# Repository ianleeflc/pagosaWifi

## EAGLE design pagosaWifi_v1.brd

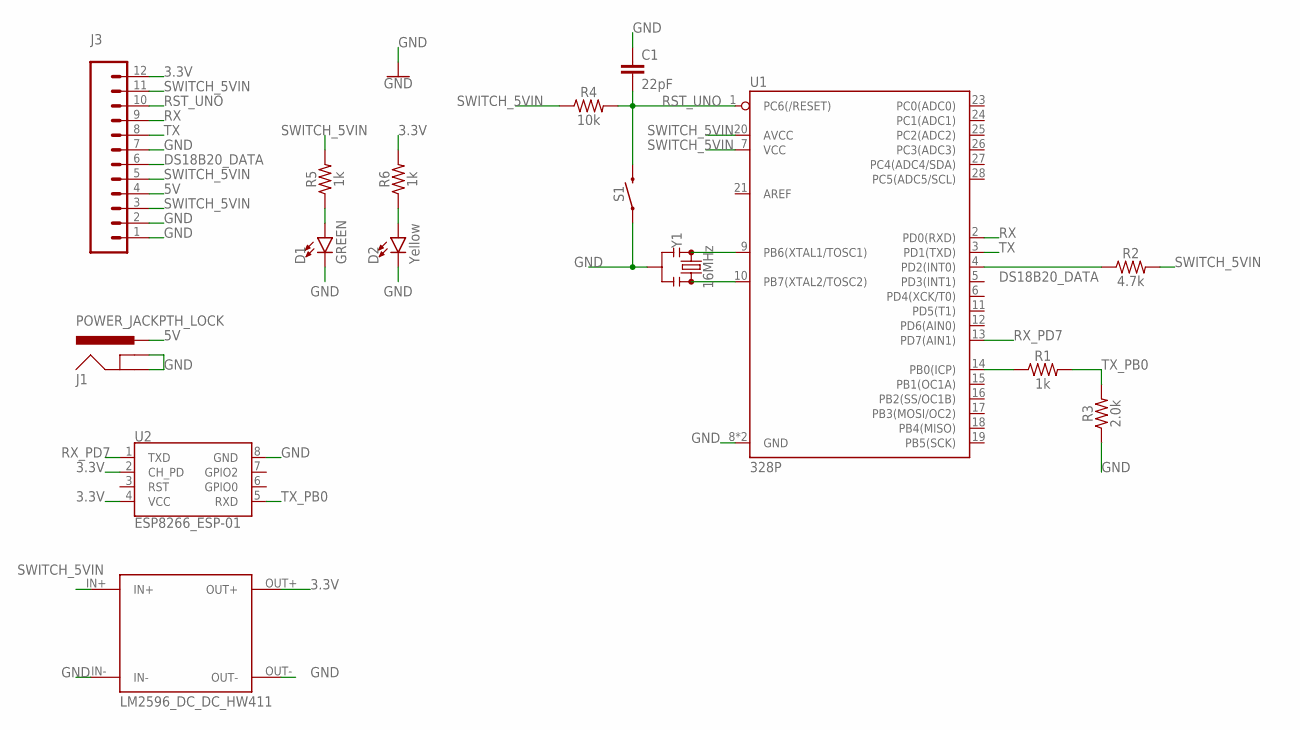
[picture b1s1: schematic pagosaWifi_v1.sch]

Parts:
C1: 22pF; 0603
D1: GREEN; LED-0603
D2: Yellow; LED-0603
J1: POWER_JACKPTH_LOCK; POWER_JACK_PTH_LOCK
J3: CONN_12; 1X12
R1, R5, R6: 1k; 0603
R2: 4.7k; 0603
R3: 2.0k; 0603
R4: 10k; 0603
S1: MOMENTARY-SWITCH-SPST-PTH-6.0MM; TACTILE_SWITCH_PTH_6.0MM
U1: 328P; DIP28
U2: ESP8266_ESP-01
U$1: LM2596_DC_DC_HW411
Y1: 16MHz; RESONATOR-SMD-3.2X1.3

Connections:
3.3V: J3.12, R6.2, U2.2 (CH_PD), U2.4 (VCC), U$1.OUT+
5V: J1.PWR, J3.4
DS18B20_DATA: J3.6, R2.1, U1.4 (PD2(INT0))
GND: C1.1, D1.C, D2.C, J1.GND, J1.GNDBREAK, J3.1, J3.2, J3.7, R3.1, S1.1, U1.8 (GND), U1.22 (GND), U2.8 (GND), U$1.IN-, U$1.OUT-, Y1.2
unnamed: U1.9 (PB6(XTAL1/TOSC1)), Y1.1
unnamed: U1.10 (PB7(XTAL2/TOSC2)), Y1.3
unnamed: R1.1, U1.14 (PB0(ICP))
unnamed: D1.A, R5.1
unnamed: D2.A, R6.1
RST_UNO: C1.2, J3.10, R4.2, S1.3 (2), U1.1 (PC6(/RESET))
RX: J3.9, U1.2 (PD0(RXD))
RX_PD7: U1.13 (PD7(AIN1)), U2.1 (TXD)
SWITCH_5VIN: J3.3, J3.5, J3.11, R2.2, R4.1, R5.2, U1.7 (VCC), U1.20 (AVCC), U$1.IN+
TX: J3.8, U1.3 (PD1(TXD))
TX_PB0: R1.2, R3.2, U2.5 (RXD)

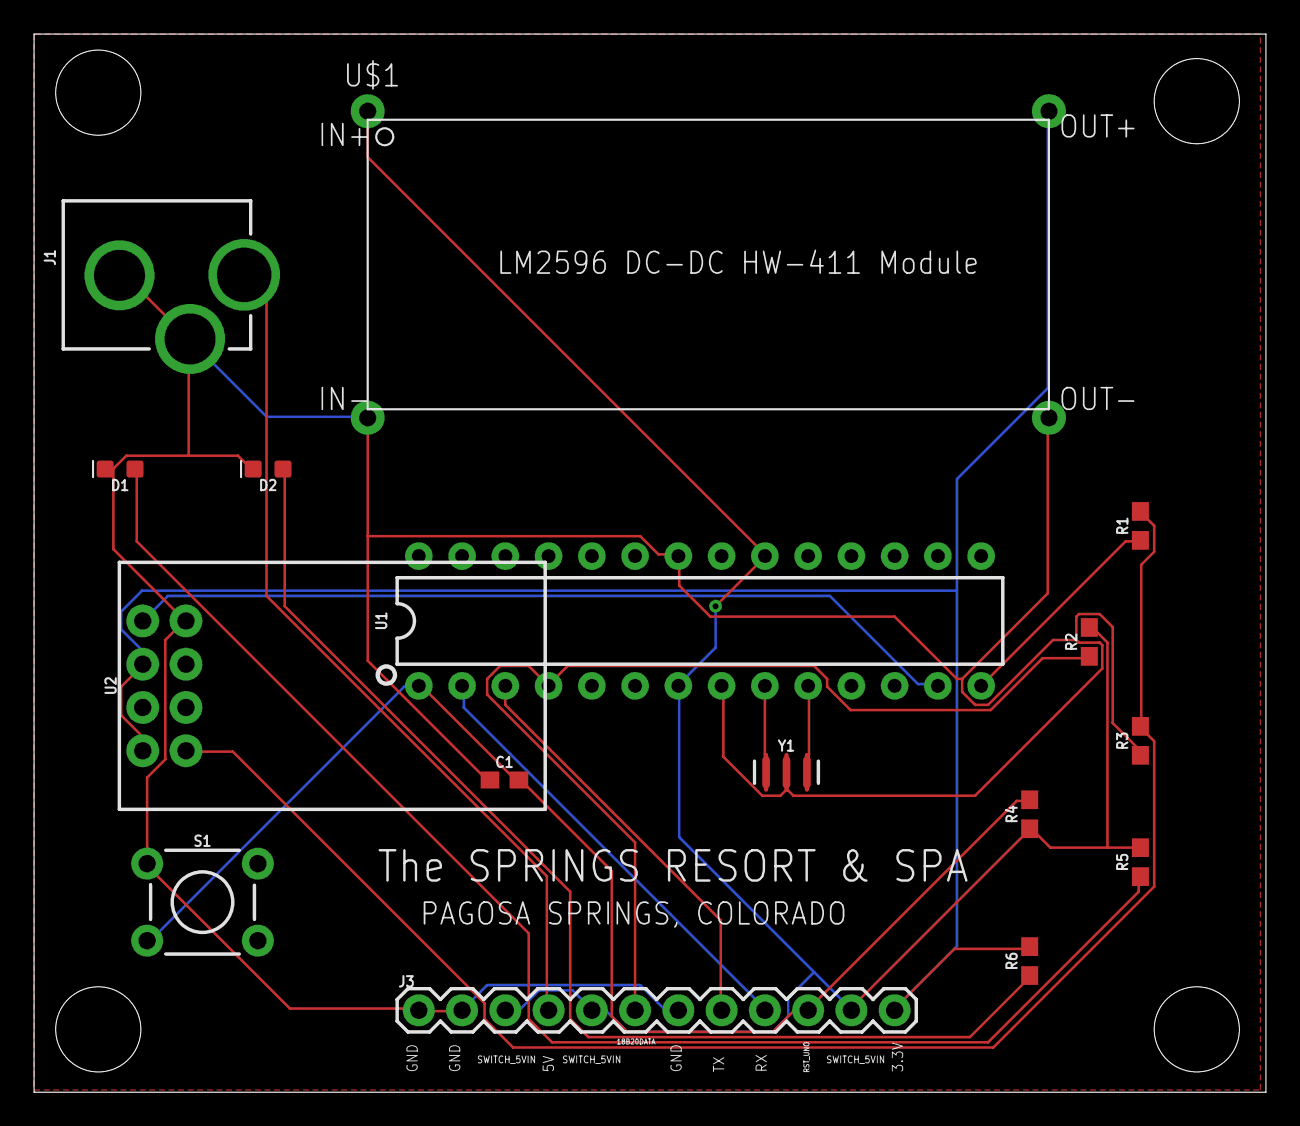
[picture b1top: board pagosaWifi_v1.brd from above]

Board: 2 copper layers, 72.3 x 62.1 mm, 16 parts (0 on the bottom side), 15 nets.

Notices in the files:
parts and their libraries:
SparkFun-Capacitors: Licensing: Creative Commons ShareAlike 4.0 International - https://creativecommons.org/licenses/by-sa/4.0
